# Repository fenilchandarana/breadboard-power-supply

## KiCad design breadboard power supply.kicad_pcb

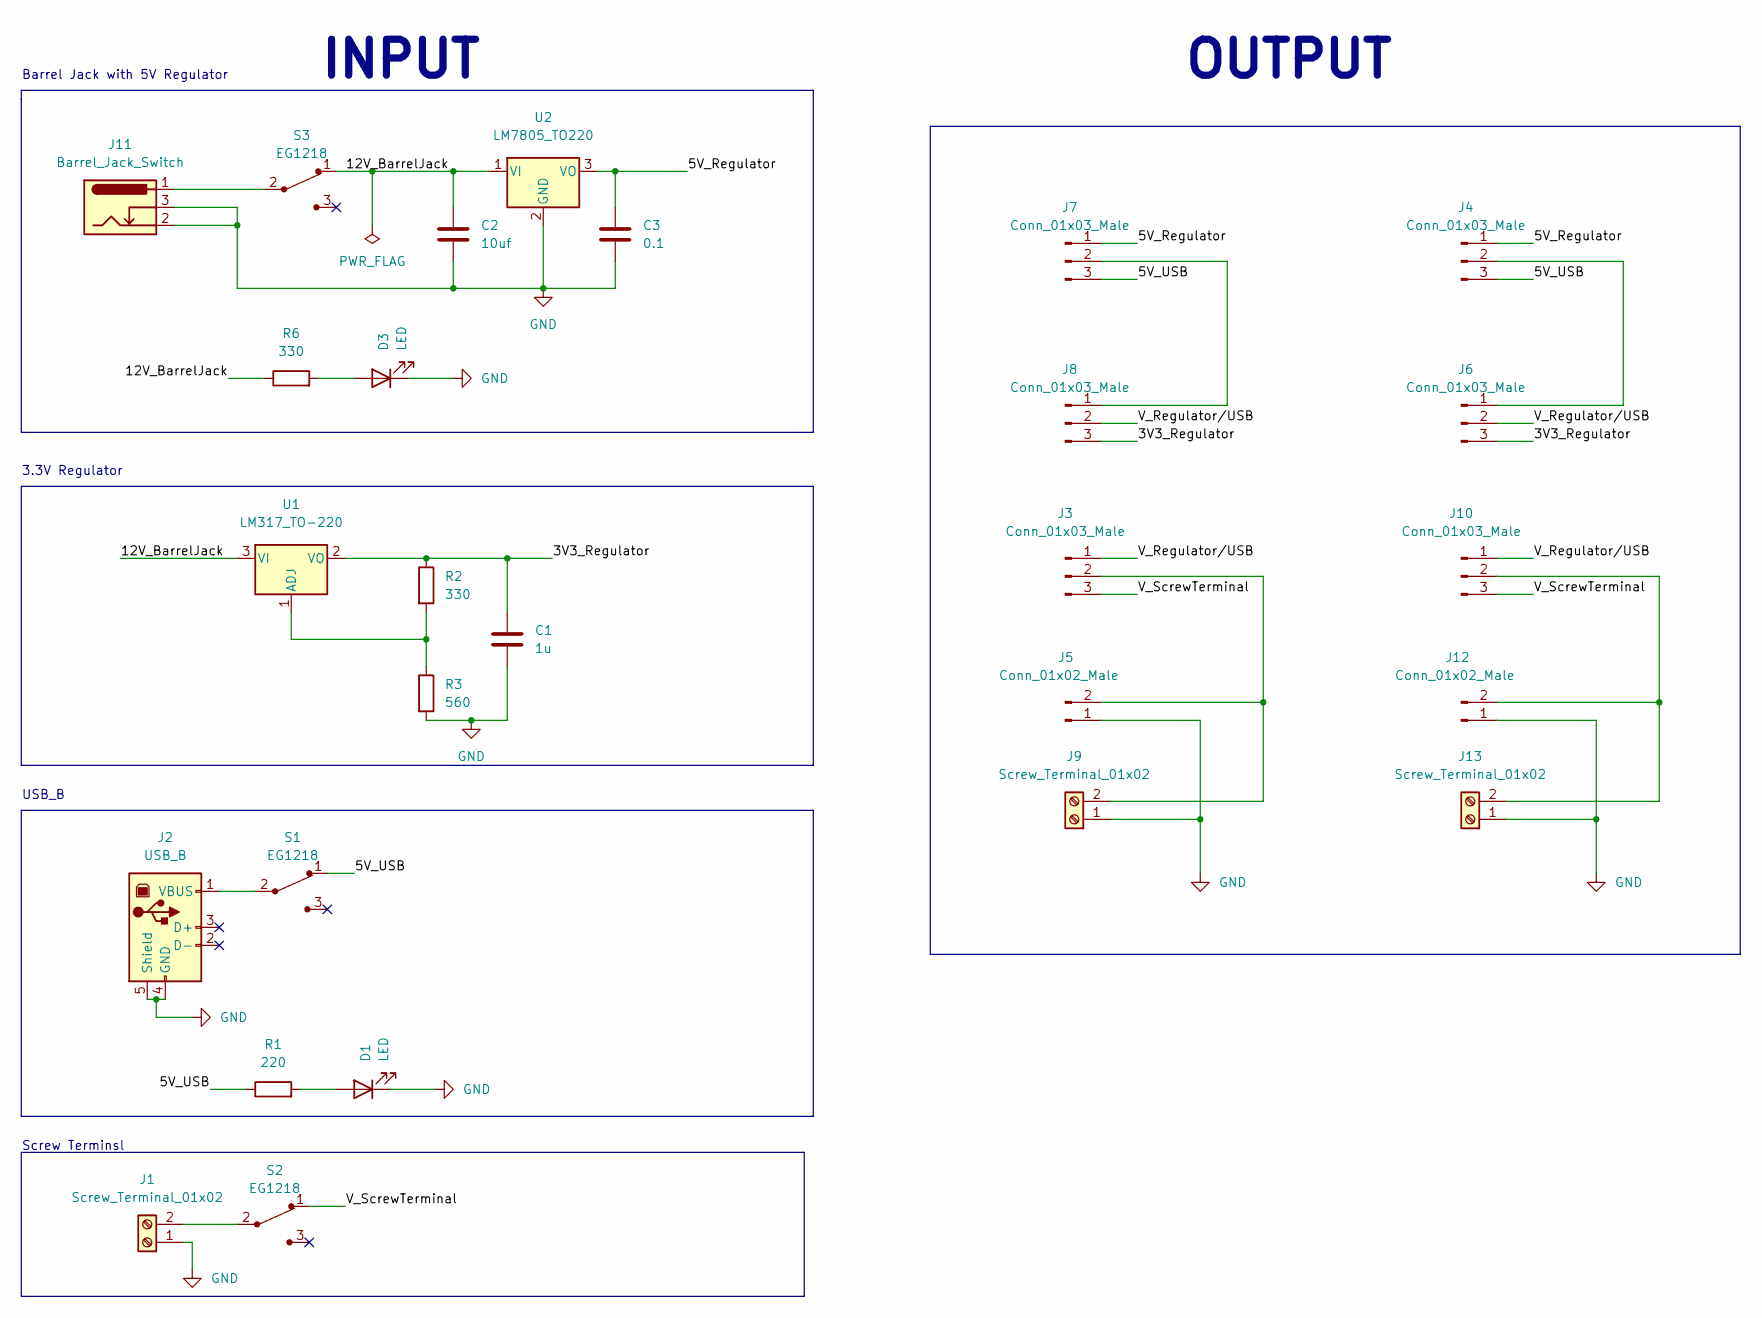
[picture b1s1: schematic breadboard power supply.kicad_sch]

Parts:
C1: 1u; C_Disc_D3.0mm_W1.6mm_P2.50mm
C2: 10uf; C_Disc_D3.0mm_W1.6mm_P2.50mm
C3: 0.1; C_Disc_D3.0mm_W1.6mm_P2.50mm
D1, D3: LED; LED_D5.0mm
J1, J9, J13: Screw_Terminal_01x02; TerminalBlock_bornier-2_P5.08mm
J2: USB_B; USB_B_Lumberg_2411_02_Horizontal
J3, J4, J6, J7, J8, J10: Conn_01x03_Male; PinHeader_1x03_P2.54mm_Vertical
J5, J12: Conn_01x02_Male; PinHeader_1x02_P2.54mm_Vertical
J11: Barrel_Jack_Switch; BarrelJack_Horizontal
R1: 220; R_Axial_DIN0204_L3.6mm_D1.6mm_P7.62mm_Horizontal
R2, R6: 330; R_Axial_DIN0204_L3.6mm_D1.6mm_P7.62mm_Horizontal
R3: 560; R_Axial_DIN0204_L3.6mm_D1.6mm_P7.62mm_Horizontal
S1, S2, S3: EG1218; Switch_Slide_11.6x4mm_EG1218; MPN EG1218; Digi-Key_PN EG1903-ND
U1: LM317_TO-220; TO-220-3_Vertical
U2: LM7805_TO220; TO-220-3_Vertical

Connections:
/3V3_Regulator: C1.1, J6.3, J8.3, R2.1, U1.2 (VO)
/5V_Regulator: C3.1, J4.1, J7.1, U2.3 (VO)
/5V_USB: J4.3, J7.3, R1.1, S1.1
/12V_BarrelJack: C2.1, R6.1, S3.1, U1.3 (VI), U2.1 (VI)
/V_Regulator/USB: J3.1, J6.2, J8.2, J10.1
/V_ScrewTerminal: J3.3, J10.3, S2.1
GND: C1.2, C2.2, C3.2, D1.1 (K), D3.1 (K), J1.1, J2.4 (GND), J2.5 (Shield), J5.1, J9.1, J11.2, J11.3, J12.1, J13.1, R3.2, U2.2 (GND)
unnamed: D1.2 (A), R1.2
unnamed: D3.2 (A), R6.2
unnamed: J1.2, S2.2
unnamed: J2.1 (VBUS), S1.2
unnamed: J3.2, J5.2, J9.2
unnamed: J4.2, J6.1
unnamed: J7.2, J8.1
unnamed: J10.2, J12.2, J13.2
unnamed: J11.1, S3.2
unnamed: R2.2, R3.1, U1.1 (ADJ)

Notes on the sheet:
USB_B
Barrel Jack with 5V Regulator
OUTPUT
3.3V Regulator
INPUT
Screw Terminsl

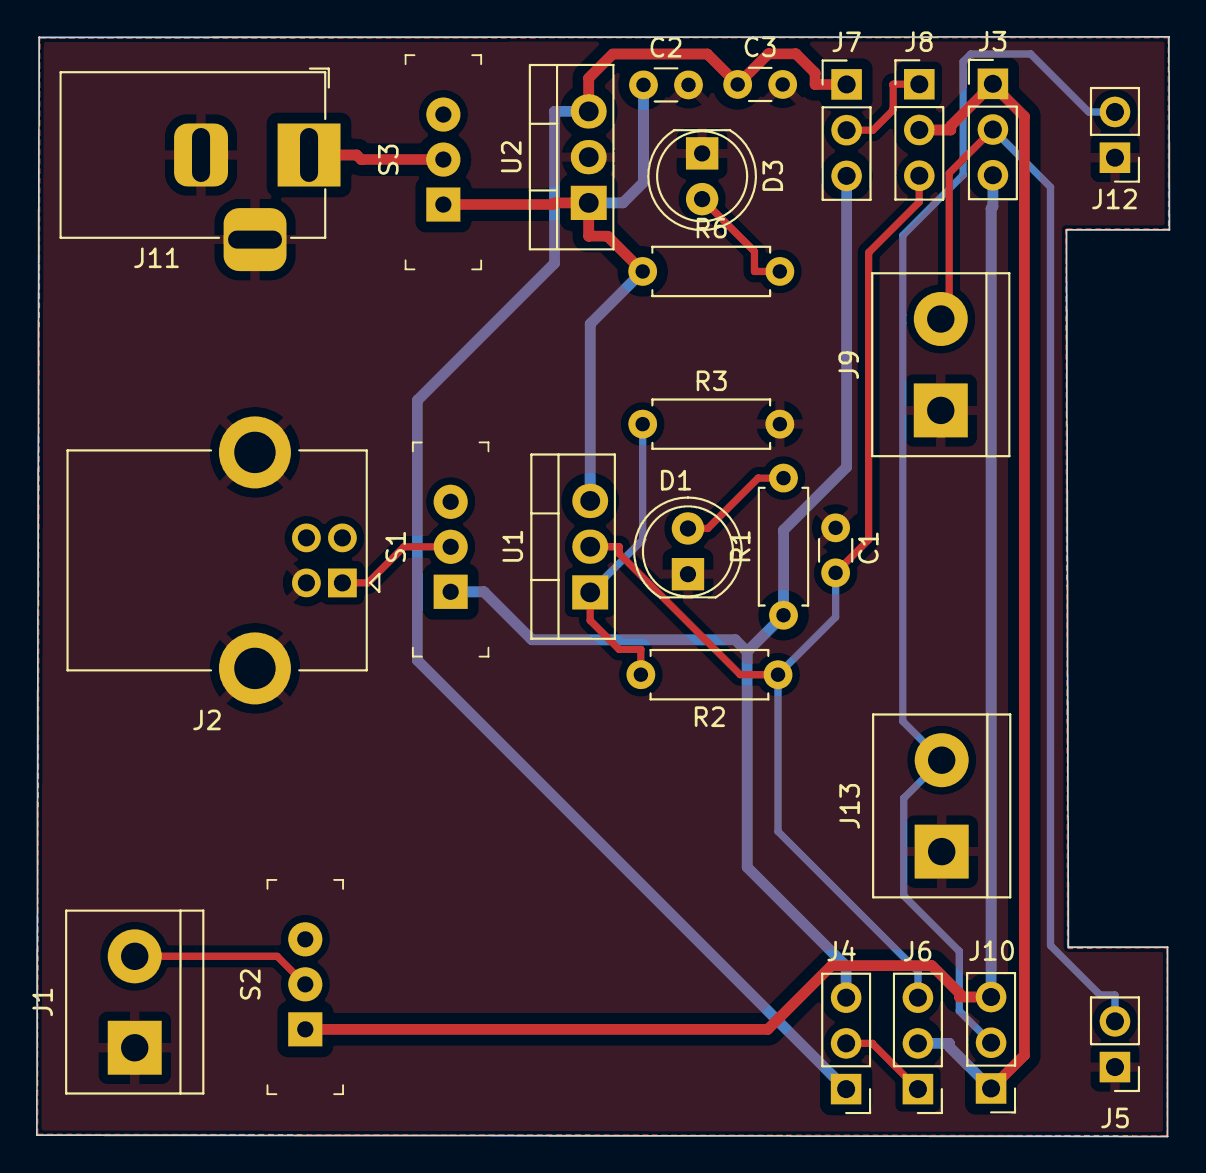
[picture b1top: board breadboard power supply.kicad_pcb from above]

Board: 2 copper layers, 62.9 x 61.1 mm, 27 parts (0 on the bottom side), 17 nets.

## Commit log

2023-02-13 blank project
2023-02-13 added usb connector for with-usb branch
2023-02-18 no changes
2023-02-18 wiring done for schematic with usb, barrel jack and screw terminal as power input. values yet to assign
2023-02-18 transferred the folder other documents into with-usb branch
2023-02-18 values assigned. annotated. text added. ERC done, no error. footprint yet to assign
2023-02-19 footprint assigned/associated
2023-02-19 reference for breadboard dimensions added in other documents
2023-02-19 deleted other document folder form main
2023-02-19 nothing major
2023-02-19 text file for dimension changed
2023-02-19 outline and constraint defined
2023-02-20 footprints arranged
2023-02-20 net classes and constraints updated
2023-02-20 power net class added
2023-02-20 board autorouted.
